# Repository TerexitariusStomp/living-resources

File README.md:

# living-resources

A living sensing commons: cheap, passive, **universal** field nodes relay
multimodal ecological detections over Reticulum to a Playnet edge, where
readings become witnessed receipts and receipts become credit for the
ecology that produced them.

License: AGPL-3.0-or-later.

## The node

One board, every lane's electronics populated (~$35–45 BOM):

camera (OV2640) · air mic (INMP441, 48 kHz/16-bit) · env
(BME280/BH1750/PIR) · hydrophone front-end · ultrasonic MEMS (20–100 kHz)
· C4D contactless front-end · 40 kHz emit transducer · microSD · Reticulum
(WiFi/LoRa/satellite)

A node's role is software + which head is in the environment — never a
different product. See `spec/living-resources.md`.

## The rules that make it a commons

- Every ecological subject is an agent with a human guardian and
  **voice 0** — it earns, it never speaks.
- `sense`/`fleet` lanes admit on **evidence** (a SAID on the lane's gate).
- `emit`/`cast`/`store` admit on **joint guardian+operator consent** —
  bio-write and cloud-write are decisions, not defaults.
- `hop`/`compute`/`engineered` refuse outright — consent is not evidence.
- Every refusal is a structured value; every emission is logged and
  receipted.

## Quickstart

```bash
make test                  # e2e under guile; static checks without it
make check-custom-budget   # the ≤5% first-party rule
```

E0 field validation (see `docs/EXPERIMENTS.md`): flash
`firmware/node/main.py` to a XIAO ESP32-S3 Sense, run the edge adapters
against the node's detection stream, score detections blinded.

## Layout

```
module/living/   specs · agents · sense-subject · attest · settlement · offers
adapters/        mic · camera · reticulum · weather   (thin seams; ML stays
                 Python-side)
firmware/node/   MicroPython universal node (incl. consent-gated EmitLane)
deploy/policies/ OPA: lane-gate.rego · consent.rego
spec/            the system spec
docs/            ARCHITECTURE (component map) · SCIENCE (claim table)
                 · EXPERIMENTS (E-gates) · ROADMAP · CONNECTOME
                 · EFFICIENCY · FUNDING (+ funding/ app drafts)
tests/e2e/       sensing-cell · refused-lanes · write-lanes
tools/edge/      classify.py (edge ML seam) · rns_edge.py (LXMF daemon)
tools/e0/        score.py (blinded field-validation scorer)
tools/e5/        relay_check.py (E5 hop-graduation harness)
```

## Non-interference

Passive by default: nothing attaches to an organism, nothing enters soil,
no anchor moorings, no flash or IR. Emission exists — it is a lane the
commons can ride — and it rides only on recorded joint consent, at
duty-cycled minimum power, with every burst on the ledger.

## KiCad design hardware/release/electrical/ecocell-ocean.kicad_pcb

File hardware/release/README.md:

# EcoCell Ocean — Engineering Release

This directory is the manufacturing package for the ocean-capable EcoCell
node: pressure-rated submerged electronics body plus a minimal-signature
tether float (GPS, antenna, solar). One serialized design covers both the
tether-float and fully submerged-pod forms — the same node electronics,
deployment role chosen by firmware flags.

## Release levels

- **R0 — prototype fab package.** A supplier-reviewable package a fab can
  quote and build from: native KiCad sources, netlist, DSN, Gerbers +
  drill, CPL, controlled BOM, assembly + harness drawings, stack-up/fab
  drawing, test plan, unit traveler, and this README with a checksummed
  manifest. R0 does **not** claim validated pressure rating, ecological
  benefit, or field performance — it claims the design files are
  consistent, DRC-clean, and buildable.
- **R1 — validated build.** R0 plus: assembled units pass TEST-PLAN,
  pressure/leak spec verified on the hull, Salton Sea serialized trial
  complete, DFM/DFT review closed with the supplier.

## Configuration identity

| Item | Value |
|---|---|
| Board | `ecocell-ocean` — 120 × 90 mm, 4-layer (F.Cu / In1 GND / In2 +3V3 / B.Cu) |
| Electrical rev | generated by `tools/pcb/gen_ocean_sch.py` + `gen_ocean_pcb.py` from the same netlist |
| Enclosure revision | `TBD` — pressure-hull + biota-disguised float CAD pending |
| Firmware revision | `firmware/node/main.py` as committed; image hash recorded per unit |
| Regional radio variant | `E22-400M22S` (433 MHz) or `E22-900M22S` (868/915) — one per build, declared |
| Approved suppliers | `TBD` — quote-backed, per-part, with lifecycle/stock check |

## Regenerating the electrical package

```
python3 tools/pcb/gen_ocean_sch.py          # writes electrical/ecocell-ocean.net
python3 tools/pcb/gen_ocean_pcb.py          # placement + DSN export
STITCH=1 python3 tools/pcb/gen_ocean_pcb.py # adds the stitch router (slow)
POST_ONLY=1 python3 tools/pcb/gen_ocean_pcb.py
    # resume: re-run only the post-attach island pass on the saved board
```

Fabrication rules baked into the generator: ≥0.2 mm clearance, ≥0.15 mm
track, 0.5/0.3 mm vias, ≥0.5 mm copper-to-edge, mounting-hole and
ESP32 antenna keepouts.

Known substitutions vs the ideal BOM:

| Ref | Part | Footprint used | Note |
|---|---|---|---|
| U_CHG | TP4056 | `SOIC-8-1EP_3.9x4.9mm_P1.27mm_EP2.41x3.81mm` | ESOP-8 footprint absent from stock KiCad libs; pin-compatible SOIC-8-EP used — verify land pattern against the chosen charger MPN before ordering |

## Release artifacts (required for R0)

| Artifact | Path / source | Status |
|---|---|---|
| Native KiCad schematic | `hardware/release/electrical/ecocell-ocean.kicad_sch` | **present** — `tools/pcb/net2sch.py` rebuilds it from `.net`; connectivity-exact (netlist round-trip: 79/79 nets, 0 diffs). Box symbols + net labels, not a redrawn sheet |
| Native KiCad PCB | `hardware/release/electrical/ecocell-ocean.kicad_pcb` | **verified** — DRC 0 unconnected / 0 errors / 0 warnings (`electrical/drc-report.txt`). **Canonical for fabrication** — `tools/pcb/gen_ocean_pcb.py` reproduces placement + route topology from the netlist, not the shipped copper; ECO fixes live only in this file |
| Gerbers + drill (or IPC-2581) | `hardware/release/electrical/fab/ecocell-ocean/` | **present** — 4-layer Gerbers + NPTH/PTH drills, sha256-manifested |
| Board stack-up / fab drawing | `hardware/release/FAB-NOTES.md` | **present** — stack-up + CAM notes; fiducials placed clear of the antenna keepout |
| Controlled BOM (MPN + alternates) | `hardware/release/electrical/ecocell-ocean-bom.csv` | **present** — generated from the netlist; MPNs/quoting unverified |
| CPL with verified origin/rotation | `hardware/release/electrical/fab/ecocell-ocean-cpl.csv` | **present** — exported from placed PCB; origin/rotation **unverified** against a supplier pick file |
| Assembly drawing | `hardware/release/assembly/` | **missing** |
| Fab quote bundle | `electrical/ecocell-ocean-fab.zip` | **present** — zipped Gerbers + drills + CPL + MANIFEST, Seeed-uploadable |
| Harness drawings | `hardware/release/HARNESS.md` | **present** — connector pinouts + tether spec from the netlist |
| Mechanical CAD + STEP + drawings | `hardware/release/mechanical/` | **present** — tube + end caps quote-ready STEP + scad source + dimensioned notes; float/dome/tether unmodeled |
| Pressure/leak spec | `hardware/release/PRESSURE-SPEC.md` | **present** — 0.4 MPa working / 0.6 MPa proof envelope; end-cap bending hand-calc closed, O-ring sizing per Parker done — FEA optional |
| Test fixture spec | `hardware/release/TEST-PLAN.md` | **present** |
| Unit traveler / calibration record | `hardware/release/UNIT-TRAVELER.md` | **present** |
| Firmware image + hash | `hardware/release/firmware-image.json` | **partial** — source-tree hash recorded; reproducible cross-build pending |
| Release manifest + checksums | `hardware/release/manifest.json` | **present** |
| DFM/DFT review record | `hardware/release/DFM-REVIEW.md` | **present** — self-review vs Seeed/JLCPCB published caps; supplier sign-off + DFT fixture still required |

No artifact may be silently replaced: any change goes through the ECO
procedure below and bumps the relevant revision.

## ECO procedure

1. Describe the change in `CHANGELOG.md` (rev, scope, reason, risk).
2. Regenerate affected artifacts from source — never hand-edit Gerbers,
   CPL, or the manifest.
3. Re-run DRC on the board and the repo checks (`make test`,
   `make check-custom-budget`); record results in the manifest.
4. Re-hash every shipped artifact into `manifest.json` and bump the
   package checksum.
5. A second reviewer signs off before the package is quoted to a fab.

## Honest-status notes

- The board validates as *fabrication-ready for a prototype lot*:
  DRC is clean (0 unconnected / 0 errors) and Gerbers + drills + CPL
  are exported and manifested. **Production** still gates on: supplier
  DFM/DFT review + quote-backed BOM, mechanical CAD (pressure hull +
  float), pressure/leak verification on the hull, a successful bring-up
  on the prototype lot, and second-reviewer sign-off per the ECO
  procedure. Never board-spun, never powered — treat the first lot as
  engineering prototypes, not saleable units.
- Acoustic playback hardware (emit lane) is consent-gated in firmware
  and policy; no ecological effect is claimed from this package.

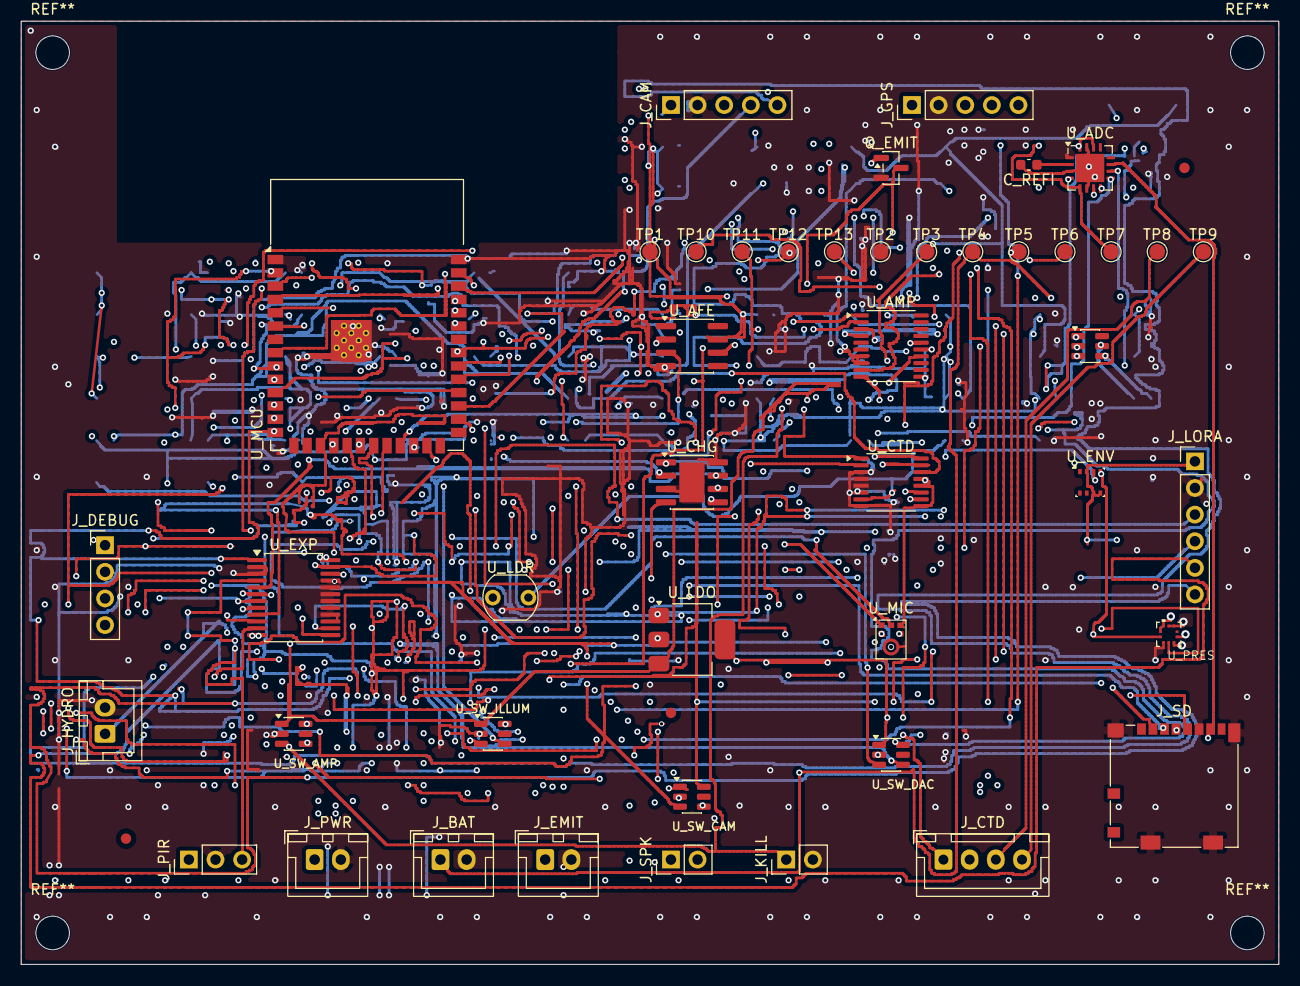
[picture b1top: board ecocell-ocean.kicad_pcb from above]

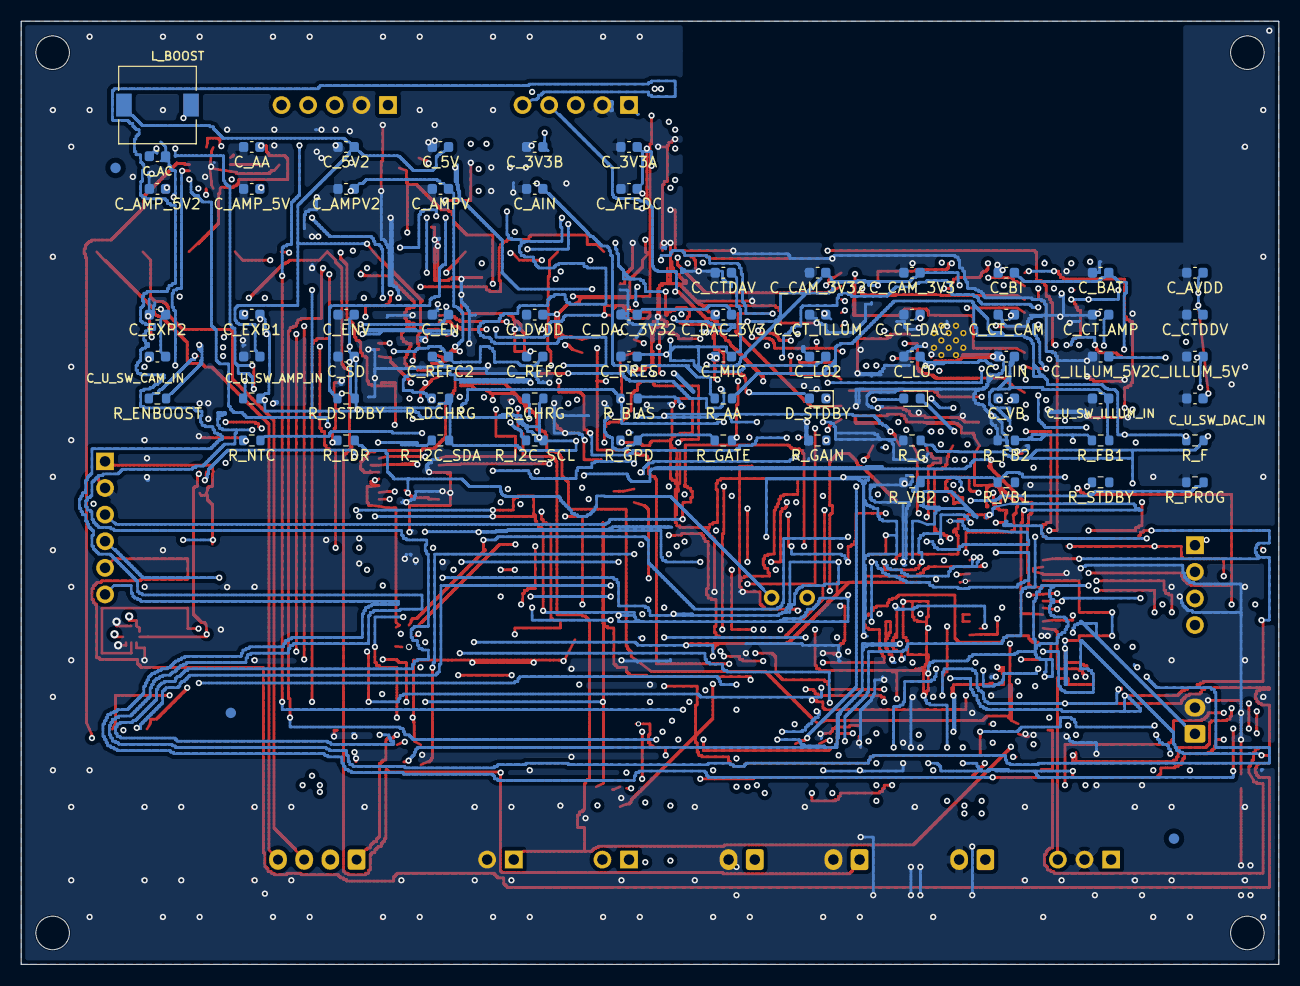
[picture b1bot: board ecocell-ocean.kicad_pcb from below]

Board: 4 copper layers, 120.0 x 90.0 mm, 121 parts (73 on the bottom side), 79 nets.

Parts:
C_3V3A, C_3V3B, C_5V, C_5V2: TPS27081A; C_0603_1608Metric
C_AA: TPS27081A; C_0603_1608Metric
C_AC: TPS27081A; C_0603_1608Metric
C_AFEDC: TPS27081A; C_0603_1608Metric
C_AIN: TPS27081A; C_0603_1608Metric
C_AMPV, C_AMPV2: TPS27081A; C_0603_1608Metric
C_AMP_5V, C_AMP_5V2: TPS27081A; C_0603_1608Metric
C_AVDD: TPS27081A; C_0603_1608Metric
C_BAT: TPS27081A; C_0603_1608Metric
C_BI: TPS27081A; C_0603_1608Metric
C_CAM_3V3, C_CAM_3V32: TPS27081A; C_0603_1608Metric
C_CTDAV: TPS27081A; C_0603_1608Metric
C_CTDDV: TPS27081A; C_0603_1608Metric
C_CT_AMP: TPS27081A; C_0603_1608Metric
C_CT_CAM: TPS27081A; C_0603_1608Metric
C_CT_DAC: TPS27081A; C_0603_1608Metric
C_CT_ILLUM: TPS27081A; C_0603_1608Metric
C_DAC_3V3, C_DAC_3V32: TPS27081A; C_0603_1608Metric
C_DVDD: TPS27081A; C_0603_1608Metric
C_EN: TPS27081A; C_0603_1608Metric
C_ENV: TPS27081A; C_0603_1608Metric
C_EXP1, C_EXP2: TPS27081A; C_0603_1608Metric
C_ILLUM_5V, C_ILLUM_5V2: TPS27081A; C_0603_1608Metric
C_LIN: TPS27081A; C_0603_1608Metric
C_LO, C_LO2: TPS27081A; C_0603_1608Metric
C_MIC: TPS27081A; C_0603_1608Metric
C_PRES: TPS27081A; C_0603_1608Metric
C_REFC, C_REFC2: TPS27081A; C_0603_1608Metric
C_REFI: 100nF; C_0603_1608Metric
C_SD: TPS27081A; C_0603_1608Metric
C_U_SW_AMP_IN: TPS27081A; C_0603_1608Metric
C_U_SW_CAM_IN: TPS27081A; C_0603_1608Metric
C_U_SW_DAC_IN: TPS27081A; C_0603_1608Metric
C_U_SW_ILLUM_IN: TPS27081A; C_0603_1608Metric
C_VB: TPS27081A; C_0603_1608Metric
D_CHRG: TPS27081A; LED_0603_1608Metric
D_STDBY: TPS27081A; LED_0603_1608Metric
FID1, FID2, FID3, FID4, FID5, FID6: Fiducial_1mm_Mask2mm
J_BAT: BAT; JST_XH_B2B-XH-A_1x02_P2.50mm_Vertical
J_CAM: CAM; PinHeader_1x05_P2.54mm_Vertical
J_CTD: CTD; JST_XH_B4B-XH-A_1x04_P2.50mm_Vertical
J_DEBUG: DEBUG; PinHeader_1x04_P2.54mm_Vertical
J_EMIT: EMIT; JST_XH_B2B-XH-A_1x02_P2.50mm_Vertical
J_GPS: GPS; PinHeader_1x05_P2.54mm_Vertical
J_HYDRO: HYDRO; JST_XH_B2B-XH-A_1x02_P2.50mm_Vertical
J_KILL: KILL; PinHeader_1x02_P2.54mm_Vertical
J_LORA: LORA; PinHeader_1x06_P2.54mm_Vertical
J_PIR: PIR; PinHeader_1x03_P2.54mm_Vertical
J_PWR: PWR; JST_XH_B2B-XH-A_1x02_P2.50mm_Vertical
J_SD: microSD; microSD_HC_Molex_104031-0811
J_SPK: SPK; PinHeader_1x02_P2.54mm_Vertical
L_BOOST: TPS27081A; L_7.3x7.3_H4.5
Q_EMIT: 2N7002; SOT-23
R_AA: TPS27081A; R_0603_1608Metric
R_BIAS: TPS27081A; R_0603_1608Metric
R_CHRG: TPS27081A; R_0603_1608Metric
R_DCHRG: TPS27081A; R_0603_1608Metric
R_DSTDBY: TPS27081A; R_0603_1608Metric
R_EN: TPS27081A; R_0603_1608Metric
R_ENBOOST: TPS27081A; R_0603_1608Metric
R_F: TPS27081A; R_0603_1608Metric
R_FB1, R_FB2: TPS27081A; R_0603_1608Metric
R_G: TPS27081A; R_0603_1608Metric
R_GAIN: TPS27081A; R_0603_1608Metric
R_GATE: TPS27081A; R_0603_1608Metric
R_GPD: TPS27081A; R_0603_1608Metric
R_I2C_SCL, R_I2C_SDA: TPS27081A; R_0603_1608Metric
R_LDR: TPS27081A; R_0603_1608Metric
R_NTC: TPS27081A; R_0603_1608Metric
R_PROG: TPS27081A; R_0603_1608Metric
R_STDBY: TPS27081A; R_0603_1608Metric
R_VB1, R_VB2: TPS27081A; R_0603_1608Metric
TP1, TP2, TP3, TP4, TP5, TP6, TP7, TP8, TP9, TP10, TP11, TP12, TP13: TP; TestPoint_Pad_D1.5mm
U_ADC: ADS8681; QFN-16-1EP_4x4mm_P0.65mm_EP2.7x2.7mm
U_AFE: OPA333; SOIC-8_3.9x4.9mm_P1.27mm
U_AMP: PCM5102A; TSSOP-20_4.4x6.5mm_P0.65mm
U_BOOST: MT3608; SOT-23-6
U_CHG: TP4056; SOIC-8-1EP_3.9x4.9mm_P1.27mm_EP2.41x3.81mm
U_CTD: ADS1220; TSSOP-16_4.4x5mm_P0.65mm
U_ENV: BME280; Bosch_LGA-8_2.5x2.5mm_P0.65mm_ClockwisePinNumbering
U_EXP: TCA9535DBT; SSOP-24_5.3x8.2mm_P0.65mm
U_LDO: AMS1117-3.3; SOT-223-3_TabPin2
U_LDR: GL5528; R_LDR_5.1x4.3mm_P3.4mm_Vertical
U_MCU: ESP32-S3-WROOM-1
U_MIC: ICS-43434; InvenSense_ICS-43434-6_3.5x2.65mm
U_PRES: BMP390; BMP390_LGA-10_2x2mm
U_SW_AMP: TPS27081A; SOT-23-6
U_SW_CAM: TPS27081A; SOT-23-6
U_SW_DAC: TPS27081A; SOT-23-6
U_SW_ILLUM: TPS27081A; SOT-23-6

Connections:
+3V3: C_3V3A.1, C_3V3B.1, C_AFEDC.1, C_AVDD.1, C_CTDAV.1, C_CTDDV.1, C_DVDD.1, C_ENV.1, C_EXP1.1, C_EXP2.1, C_LO.1, C_LO2.1, C_MIC.1, C_PRES.1, C_SD.1, C_U_SW_CAM_IN.1, C_U_SW_DAC_IN.1, J_DEBUG.1, J_GPS.1, J_LORA.1, J_PIR.1, J_SD.4, R_CHRG.1, R_DCHRG.1, R_DSTDBY.1, R_EN.1, R_I2C_SCL.1, R_I2C_SDA.1, TP1.1, U_ADC.14, U_ADC.16, U_AFE.7, U_AMP.4, U_CTD.9, U_CTD.12, U_CTD.13, U_ENV.2, U_ENV.5, U_ENV.6, U_EXP.24, U_LDO.2, U_LDR.1, U_MCU.2, U_MIC.5, U_PRES.1, U_PRES.6, U_PRES.10, U_SW_CAM.1, U_SW_DAC.1
+5V: C_5V.1, C_5V2.1, C_LIN.1, C_U_SW_AMP_IN.1, C_U_SW_ILLUM_IN.1, L_BOOST.2, R_FB1.1, TP3.1, U_LDO.3, U_SW_AMP.1, U_SW_ILLUM.1
ADC_AIN: C_AA.1, C_AIN.1, R_AA.2, TP7.1, U_ADC.5
ADC_RST: U_ADC.7, U_MCU.8
ADS_CS: U_CTD.2, U_MCU.25
ADS_DIN: U_CTD.16, U_MCU.23
ADS_DOUT: U_CTD.15, U_MCU.24
ADS_DRDY: U_CTD.14, U_MCU.28
ADS_SCK: U_CTD.1, U_MCU.11
AFE_INP: C_AC.2, R_BIAS.2, U_AFE.3
AFE_N: R_F.1, R_G.1, U_AFE.2
AFE_OUT: R_AA.1, R_F.2, TP6.1, U_AFE.6
AMP_5V: C_AMPV.1, C_AMPV2.1, C_AMP_5V.1, C_AMP_5V2.1, U_AMP.7, U_AMP.8, U_SW_AMP.6
CAM_3V3: C_CAM_3V3.1, C_CAM_3V32.1, J_CAM.1, U_SW_CAM.6
CAM_RST: J_CAM.5, U_EXP.11
CHRG_ST: D_CHRG.1, R_CHRG.2, U_CHG.7, U_EXP.5
CTD_EXC_N: J_CTD.4, TP9.1
CTD_EXC_P: J_CTD.3, TP8.1
CTD_S_N: J_CTD.2, U_CTD.10
CTD_S_P: J_CTD.1, U_CTD.11
CT_AMP: C_CT_AMP.1, U_SW_AMP.4
CT_CAM: C_CT_CAM.1, U_SW_CAM.4
CT_DAC: C_CT_DAC.1, U_SW_DAC.4
CT_ILLUM: C_CT_ILLUM.1, U_SW_ILLUM.4
DAC_3V3: C_DAC_3V3.1, C_DAC_3V32.1, U_SW_DAC.6
DEBUG_RX: J_DEBUG.4, U_MCU.36
DEBUG_TX: J_DEBUG.3, U_MCU.37
EMIT_GATE: Q_EMIT.1, R_GATE.2, R_GPD.1
EMIT_PWM: R_GATE.1, U_MCU.39
EMIT_SIG: J_EMIT.1, Q_EMIT.3
EN: C_EN.1, R_EN.2, U_MCU.3
EN_AMP: J_KILL.1, TP11.1, U_EXP.8, U_SW_AMP.3
EN_BOOST: R_ENBOOST.2, U_BOOST.4
EN_CAM: TP10.1, U_EXP.7, U_SW_CAM.3
EN_ILLUM: TP12.1, U_EXP.9, U_SW_ILLUM.3
EN_PLAY: TP13.1, U_EXP.10, U_SW_DAC.3
EXP_INT: U_EXP.1, U_MCU.14
FB: R_FB1.2, R_FB2.1, U_BOOST.3
GAIN_SLOT: R_GAIN.1, U_AMP.2
GND: C_3V3A.2, C_3V3B.2, C_5V.2, C_5V2.2, C_AA.2, C_AFEDC.2, C_AIN.2, C_AMPV.2, C_AMPV2.2, C_AMP_5V.2, C_AMP_5V2.2, C_AVDD.2, C_BAT.2, C_BI.2, C_CAM_3V3.2, C_CAM_3V32.2, C_CTDAV.2, C_CTDDV.2, C_CT_AMP.2, C_CT_CAM.2, C_CT_DAC.2, C_CT_ILLUM.2, C_DAC_3V3.2, C_DAC_3V32.2, C_DVDD.2, C_EN.2, C_ENV.2, C_EXP1.2, C_EXP2.2, C_ILLUM_5V.2, C_ILLUM_5V2.2, C_LIN.2, C_LO.2, C_LO2.2, C_MIC.2, C_PRES.2, C_REFC.2, C_REFC2.2, C_REFI.2, C_SD.2, C_U_SW_AMP_IN.2, C_U_SW_CAM_IN.2, C_U_SW_DAC_IN.2, C_U_SW_ILLUM_IN.2, C_VB.2, J_BAT.2, J_CAM.2, J_DEBUG.2, J_EMIT.2, J_GPS.2, J_HYDRO.2, J_KILL.2, J_LORA.2, J_PIR.2, J_PWR.2, J_SD.6, J_SD.SH, Q_EMIT.2, R_FB2.2, R_G.2, R_GAIN.2, R_GPD.2, R_LDR.2, R_NTC.2, R_PROG.2, R_VB2.2, TP2.1, U_ADC.1, U_ADC.3, U_ADC.6, U_ADC.15, U_ADC.17, U_AFE.4, U_AMP.3, U_AMP.11, U_AMP.15, U_BOOST.2, U_CHG.3, U_CHG.8, U_CHG.9, U_CTD.3, U_CTD.4, U_CTD.5, U_CTD.6, U_CTD.8, U_EXP.2, U_EXP.3, U_EXP.12, U_EXP.15, U_EXP.16, U_EXP.17, U_EXP.18, U_EXP.19, U_EXP.20, U_EXP.21, U_LDO.1, U_MCU.1, U_MCU.40, U_MCU.41, U_MIC.2, U_MIC.3, U_PRES.3, U_PRES.5, U_PRES.8, U_PRES.9, U_SW_AMP.2, U_SW_CAM.2, U_SW_DAC.2, U_SW_ILLUM.2
HYDRO_SIG: C_AC.1, J_HYDRO.1
I2C_SCL: R_I2C_SCL.2, U_ENV.4, U_EXP.22, U_MCU.17, U_PRES.2
I2C_SDA: R_I2C_SDA.2, U_ENV.3, U_EXP.23, U_MCU.12, U_PRES.4
I2S0_BCLK: U_MCU.18, U_MIC.4
I2S0_SD: U_MCU.13, U_MIC.6
I2S0_WS: U_MCU.10, U_MIC.1
I2S1_BCLK: U_AMP.16, U_MCU.4
I2S1_DIN: U_AMP.1, U_MCU.6
I2S1_LRCK: U_AMP.14, U_MCU.5
ILLUM_5V: C_ILLUM_5V.1, C_ILLUM_5V2.1, U_SW_ILLUM.6
LDR_OUT: R_LDR.1, U_CTD.7, U_LDR.2
LED_CHRG_A: D_CHRG.2, R_DCHRG.2
LED_STDBY_A: D_STDBY.2, R_DSTDBY.2
LORA_M0: J_LORA.5, U_EXP.13
LORA_M1: J_LORA.6, U_EXP.14
NTC: R_NTC.1, U_CHG.1
PIR_OUT: J_PIR.3, U_EXP.4
PPS: J_GPS.5, U_MCU.29
PROG: R_PROG.1, U_CHG.2
REFCAP: C_REFC.1, C_REFC2.1, U_ADC.4
REFIO: C_REFI.1, U_ADC.2
SD_CS: J_SD.2, U_MCU.38
SPI2_CS: U_ADC.9, U_MCU.22
SPI2_MISO: J_SD.7, U_ADC.11, U_MCU.21
SPI2_MOSI: J_SD.3, U_ADC.8, U_MCU.19
SPI2_SCK: J_SD.5, U_ADC.10, U_MCU.20
SPK_N: J_SPK.2, U_AMP.10
SPK_P: J_SPK.1, U_AMP.9
STDBY_ST: D_STDBY.1, R_STDBY.2, U_CHG.6, U_EXP.6
SW: L_BOOST.1, U_BOOST.1
UART1_RX: J_LORA.3, U_MCU.30
UART1_TX: J_LORA.4, U_MCU.33
UART2_RX: J_GPS.3, U_MCU.31
UART2_TX: J_GPS.4, U_MCU.35
UART3_RX: J_CAM.3, U_MCU.32
UART3_TX: J_CAM.4, U_MCU.9
VBAT: C_BAT.1, C_BI.1, J_BAT.1, R_ENBOOST.1, TP4.1, U_BOOST.5, U_CHG.5
VBIAS: C_VB.1, R_BIAS.1, R_VB1.2, R_VB2.1, TP5.1
VIN: J_PWR.1, U_CHG.4

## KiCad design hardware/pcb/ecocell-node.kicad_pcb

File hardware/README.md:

# hardware/ — EcoCell universal node

One board design. Every lane's electronics on every unit. Role =
firmware config + which head sits in the environment — never a variant,
never an upgrade purchase.

## What to read in what order

| File | For |
|---|---|
| `BOM.md` | What to buy — core board + every head + per-deployment kits |
| `FIELD-KIT.md` | **Complete sourcing matrix** — Seeed-assembled vs plug-in vs field kit, first-article test plan |
| `PROVISIONING.md` | **Parcel→live node** — flash, identity, consent defaults, edge pairing, commissioning |
| `PINOUT.md` | How it wires — the pin map the firmware and heads share |
| `ASSEMBLY.md` | How to build — solder points, flash steps, bench test |
| `ENCLOSURE.md` | How to deploy — garden / shore-dock / reef-float / submerged forms |
| `DATASHEET.md` | The tender-attachable product sheet (prospective — v1 target) |
| `PCB.md` | **Manufacturable carrier** — KiCad source, DRC-clean Gerbers, Seeed ordering |
| `diagrams/wiring.svg` | **Visual: full wiring diagram** — every pin→head wire, net colors |
| `diagrams/layout.svg` | **Visual: carrier top-view** — component placement on perfboard |
| `diagrams/enclosure-forms.svg` | **Visual: 4 cross-sections** — garden/shore/float/pod |

## The build in one picture

```
        ┌──────────────────── XIAO ESP32-S3 Sense ───────────────────┐
        │  onboard: OV2640 camera · PDM mic · microSD · ESP32-S3     │
        │                                                           │
  D0 PIR wake ──┐            ┌── D4/D5  I2C bus ──────────────────┐  │
  D1 hydro ADC  │            │  BME280 · BH1750 · AD7746 (C4D)    │  │
  D2 ultra ADC  │            └────────────────────────────────────┘  │
  D3 emit PWM ──┼──▶ 40 kHz transducer driver (consent-gated)        │
  D6/D7 UART ───┼──▶ LoRa RNode / satellite modem / serial gateway   │
  D8–D10 SPI ───┴──▶ spare (expansion: second SD, display, GPS)      │
        └───────────────────────────────────────────────────────────┘
```

## Two build paths

1. **Hand build (v1, now):** XIAO ESP32-S3 Sense + breakout modules on
   headers — no PCB fab needed, ~1–2 h per unit, ~$35–45.
2. **Carrier board (v2, tender path):** `pcb/` holds a **DRC-clean,
   fab-ready KiCad design** — upload `gerbers/ecocell-carrier-gerbers.zip`
   to Seeed Fusion (2-layer, 100×80, standard spec). v2 adds the field
   layer: screw-terminal 5V input, fuse, reverse-polarity Schottky, rail
   TVS, ESD clamps on the head inputs, power LED, fiducials. See `PCB.md`
   for the package and `FIELD-KIT.md` for everything else a deployable
   node still needs (XIAO, heads, radio, power, enclosure).

## Honest flags

- Pin assignments in `PINOUT.md` are the recommended map — **verify the
  free-GPIO set against your board revision's schematic** (XIAO Sense
  expansion board occupies internal pins for camera/mic/SD).
- The ultrasonic lane's 20–100 kHz band exceeds what the ESP32 ADC path
  samples comfortably — the head and wiring are ready; firmware capture
  may need decimation tricks or the C++ firmware variant. Noted in
  `PINOUT.md`, not hidden.
- Emit lane: hardware is live on every board; activation is purely a
  consent flag — see `deploy/policies/living/` and `firmware/node/main.py`.

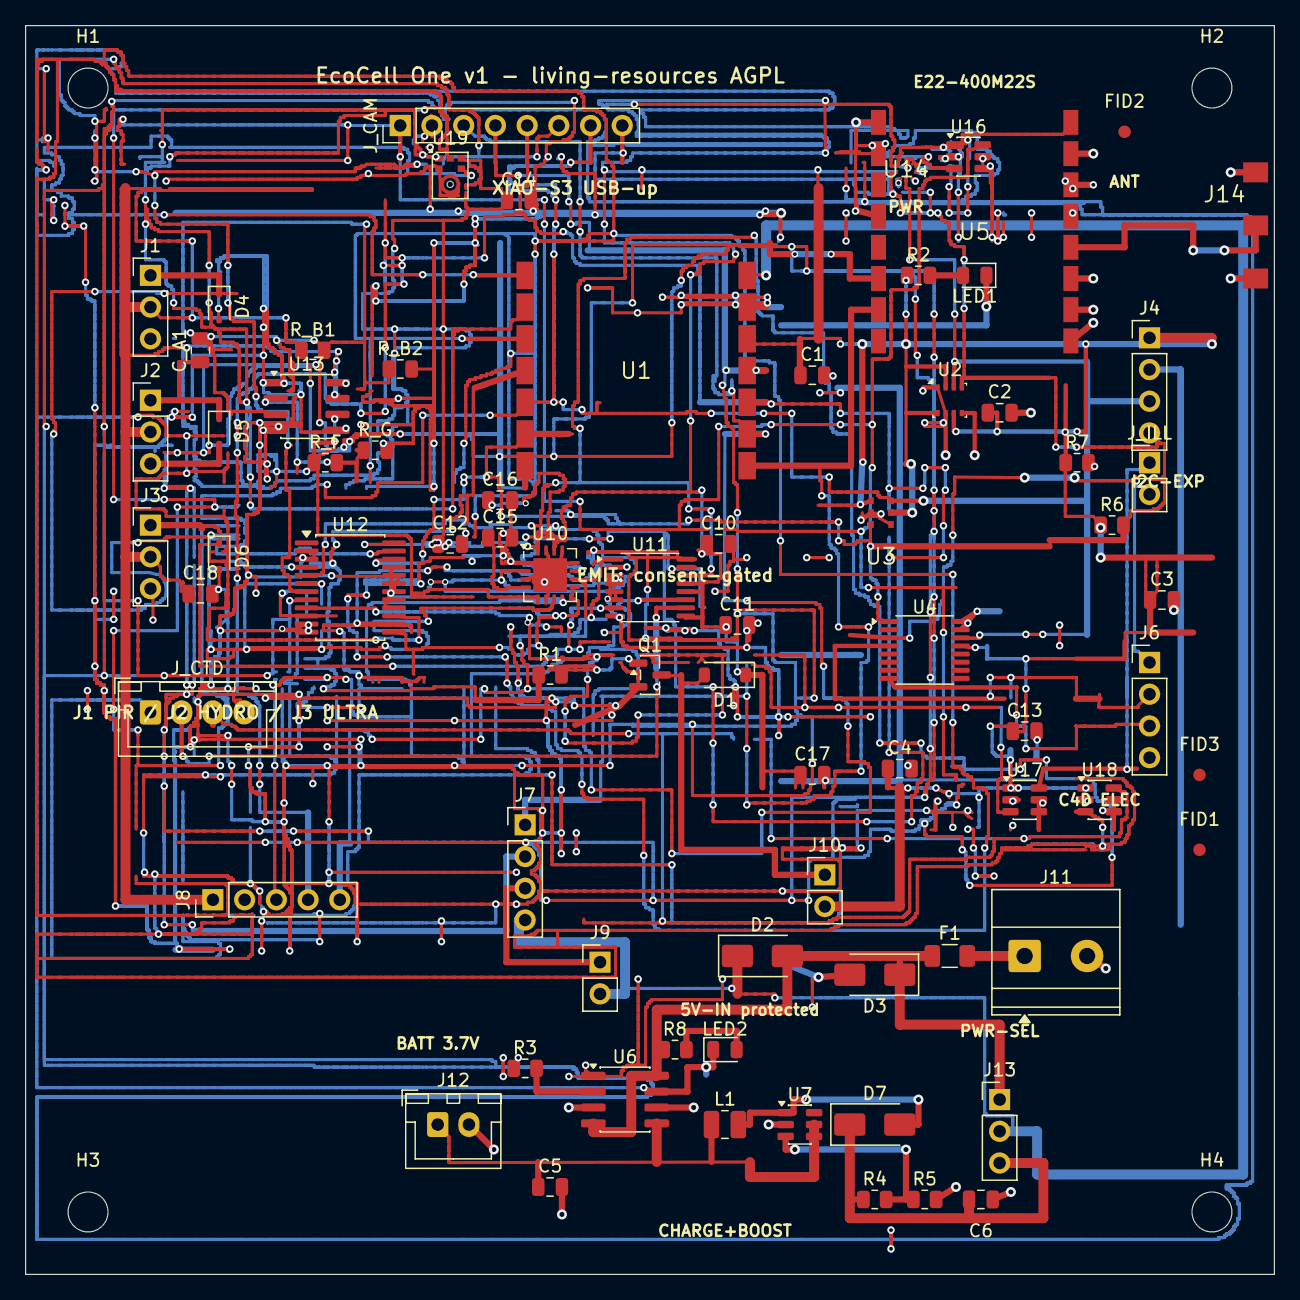
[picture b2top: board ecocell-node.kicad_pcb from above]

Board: 2 copper layers, 100.0 x 100.0 mm, 79 parts (0 on the bottom side), 51 nets.

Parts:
C1, C2, C3, C4, C10, C11, C12, C13, C14, C17, C18: 100nF; C_0805_2012Metric
C5, C6: 22uF; C_0805_2012Metric
C15, C16: 10uF; C_0805_2012Metric
C_A1: 1uF; C_0805_2012Metric
D1: 1N4148W; D_SOD-123
D2, D7: SS14; D_SMA
D3: SMAJ5.0A; D_SMA
D4, D5, D6: PESD5V0; D_SOD-323
F1: 0.75A; Fuse_1206_3216Metric
FID1, FID2, FID3: FID; Fiducial_1mm_Mask3mm
H1, H2, H3, H4: M3; MountingHole_3.2mm_M3
J1: PIR; PinHeader_1x03_P2.54mm_Vertical
J2: HYDRO; PinHeader_1x03_P2.54mm_Vertical
J3: ULTRA; PinHeader_1x03_P2.54mm_Vertical
J4: I2C-EXP; PinHeader_1x04_P2.54mm_Vertical
J6: C4D-ELEC; PinHeader_1x04_P2.54mm_Vertical
J7: UART; PinHeader_1x04_P2.54mm_Vertical
J8: SPI; PinHeader_1x05_P2.54mm_Vertical
J9: 5V-IN; PinHeader_1x02_P2.54mm_Vertical
J10: EMIT-40k; PinHeader_1x02_P2.54mm_Vertical
J11: 5V-SCREW; TerminalBlock_Phoenix_MKDS-1,5-2_1x02_P5.00mm_Horizontal
J12: BATT-3.7V; JST_XH_B2B-XH-A_1x02_P2.50mm_Vertical
J13: PWR-SEL; PinHeader_1x03_P2.54mm_Vertical
J14: SMA-EDGE
J_CAM: CAM-SPI; PinHeader_1x08_P2.54mm_Vertical
J_CTD: CTD; JST_XH_B4B-XH-A_1x04_P2.50mm_Vertical
J_ILL: ILLUM; PinHeader_1x02_P2.54mm_Vertical
L1: 22uH; L_1008_2520Metric
LED1: PWR-GRN; LED_0805_2012Metric
LED2: CHRG-RED; LED_0805_2012Metric
Q1: 2N7002; SOT-23
R1: 100R; R_0805_2012Metric
R2, R8: 1k; R_0805_2012Metric
R3: 1.2k; R_0805_2012Metric
R4: 75k; R_0805_2012Metric
R5: 10k; R_0805_2012Metric
R6, R7: 4.7k; R_0805_2012Metric
R_B1, R_B2: 100k; R_0805_2012Metric
R_F: 49.9k; R_0805_2012Metric
R_G: 1k; R_0805_2012Metric
U1: XIAO-ESP32S3
U2: BME280; Bosch_LGA-8_2.5x2.5mm_P0.65mm_ClockwisePinNumbering
U3: BH1750
U4: AD7746; TSSOP-16_4.4x5mm_P0.65mm
U5: E22-400M22S
U6: TP4056; SOP-8_3.76x4.96mm_P1.27mm
U7: MT3608; SOT-23-6
U10: ADS8681; QFN-16-1EP_4x4mm_P0.65mm_EP2.7x2.7mm
U11: ADS1220; TSSOP-16_4.4x5mm_P0.65mm
U12: TCA9535; SSOP-24_5.3x8.2mm_P0.65mm
U13: OPA333; SOIC-8_3.9x4.9mm_P1.27mm
U14: BMP390; BMP390_LGA-10_2x2mm
U16, U17, U18: TPS27081A; SOT-23-6
U19: ICS-43434; InvenSense_ICS-43434-6_3.5x2.65mm

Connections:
+3V3: C1.1, C2.1, C3.1, C4.1, C10.1, C11.1, C12.1, C13.1, C14.1, C17.1, C18.1, D1.1, J1.2, J2.2, J3.2, J4.1, J8.1, J10.2, R2.1, R6.1, R7.1, R_B1.1, U1.10, U2.2, U2.6, U2.8, U3.1, U3.5, U4.13, U5.9, U10.14, U10.16, U11.9, U11.12, U11.13, U12.24, U13.7, U14.1, U14.6, U14.10, U16.1, U17.1, U18.1, U19.5
+5V: D2.1, J7.4, J9.2, J13.2, U1.8
ADC_CS: U10.9, U12.13
ADC_RST: U10.7, U12.6
AFE_INP: C_A1.2, R_B1.2, R_B2.1, U13.3
AFE_N: R_F.2, R_G.1, U13.2
AFE_SRC: C_A1.1, D5.1, J2.1
AIN: R_F.1, U10.5, U13.6
ANT: J14.1, U5.13
CAM_3V3: J_CAM.1, U16.6
CAM_CS: J_CAM.6, U12.7
CHRG_LED: LED2.2, R8.2
CHRG_N: LED2.1, U6.7, U12.15
CIN_P: J6.3, U4.8
CTDEXC: J_CTD.3, U18.6
CTD_CS: U11.2, U12.14
CTD_DRDY: U11.14, U12.5
CTD_N: J_CTD.2, U11.10
CTD_P: J_CTD.1, U11.11
D3_EMIT: R1.1, U1.4
EMIT_GATE: Q1.1, R1.2
EMIT_SW: D1.2, J10.1, Q1.3
EN_CAM: U12.8, U16.3
EN_CTD: U12.10, U18.3
EN_ILLUM: U12.9, U17.3
EXC_A: J6.1, U4.3
EXC_B: J6.2, U4.4
FB_NODE: R4.2, R5.1, U7.3
GND: C1.2, C2.2, C3.2, C4.2, C5.2, C6.2, C10.2, C11.2, C12.2, C13.2, C14.2, C15.2, C16.2, C17.2, C18.2, D3.2, D4.2, D5.2, D6.2, J1.3, J2.3, J3.3, J4.2, J6.4, J7.3, J8.2, J9.1, J11.2, J12.2, J14.2, J_CAM.2, J_CTD.4, J_ILL.2, LED1.1, Q1.2, R3.1, R5.2, R_B2.2, R_G.2, U1.9, U2.1, U2.5, U2.7, U3.2, U3.4, U4.15, U4.16, U5.1, U5.2, U5.4, U5.10, U5.11, U5.12, U5.14, U5.15, U5.16, U6.1, U6.3, U6.6, U7.2, U10.1, U10.3, U10.6, U10.12, U10.13, U10.15, U10.17, U11.3, U11.4, U11.5, U11.6, U11.8, U12.2, U12.3, U12.11, U12.12, U12.16, U12.17, U12.18, U12.19, U12.20, U12.21, U13.1, U13.4, U13.5, U13.8, U14.3, U14.5, U14.7, U14.8, U14.9, U16.2, U16.4, U16.5, U17.2, U17.4, U17.5, U18.2, U18.4, U18.5, U19.2, U19.3
I2S_BCK: U1.1, U19.4
I2S_SD: U1.3, U19.6
I2S_WS: U1.2, U19.1
ILLUM_3V3: J_ILL.1, U17.6
LEDPWR: LED1.2, R2.2
MISO_D9: J8.4, J_CAM.5, U1.12, U10.11, U11.15
MOSI_D10: J8.3, J_CAM.4, U1.11, U10.8, U11.16
PIR_IN: D4.1, J1.1, U12.4
PROG_N: R3.2, U6.2
REFCAP: C15.1, U10.4
REFIO: C16.1, U10.2
RX_D7: J7.1, U1.14, U5.7
SCK_D8: J8.5, J_CAM.3, U1.13, U10.10, U11.1
SCL: J4.4, J_CAM.8, R6.2, U1.6, U2.4, U3.3, U4.1, U12.22, U14.2
SDA: J4.3, J_CAM.7, R7.2, U1.5, U2.3, U3.6, U4.14, U12.23, U14.4
SW_NODE: D7.2, L1.2, U7.1
TX_D6: J7.2, U1.7, U5.6
ULT_AIN: D6.1, J3.1, U11.7
VBATT: C5.1, J12.1, L1.1, U6.5, U7.4, U7.5
VBOOST: C6.1, D7.1, J13.3, R4.1
VIN: F1.2, J11.1
VPROT: D2.2, D3.1, F1.1, J13.1, R8.1, U6.4, U6.8

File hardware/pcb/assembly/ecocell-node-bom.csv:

Reference,Value,Footprint
C1,100nF,C_0805_2012Metric
C10,100nF,C_0805_2012Metric
C11,100nF,C_0805_2012Metric
C12,100nF,C_0805_2012Metric
C13,100nF,C_0805_2012Metric
C14,100nF,C_0805_2012Metric
C15,10uF,C_0805_2012Metric
C16,10uF,C_0805_2012Metric
C17,100nF,C_0805_2012Metric
C18,100nF,C_0805_2012Metric
C2,100nF,C_0805_2012Metric
C3,100nF,C_0805_2012Metric
C4,100nF,C_0805_2012Metric
C5,22uF,C_0805_2012Metric
C6,22uF,C_0805_2012Metric
C_A1,1uF,C_0805_2012Metric
D1,1N4148W,D_SOD-123
D2,SS14,D_SMA
D3,SMAJ5.0A,D_SMA
D4,PESD5V0,D_SOD-323
D5,PESD5V0,D_SOD-323
D6,PESD5V0,D_SOD-323
D7,SS14,D_SMA
F1,0.75A,Fuse_1206_3216Metric
J1,PIR,PinHeader_1x03_P2.54mm_Vertical
J10,EMIT-40k,PinHeader_1x02_P2.54mm_Vertical
J11,5V-SCREW,"TerminalBlock_Phoenix_MKDS-1,5-2_1x02_P5.00mm_Horizontal"
J12,BATT-3.7V,JST_XH_B2B-XH-A_1x02_P2.50mm_Vertical
J13,PWR-SEL,PinHeader_1x03_P2.54mm_Vertical
J14,SMA-EDGE,
J2,HYDRO,PinHeader_1x03_P2.54mm_Vertical
J3,ULTRA,PinHeader_1x03_P2.54mm_Vertical
J4,I2C-EXP,PinHeader_1x04_P2.54mm_Vertical
J6,C4D-ELEC,PinHeader_1x04_P2.54mm_Vertical
J7,UART,PinHeader_1x04_P2.54mm_Vertical
J8,SPI,PinHeader_1x05_P2.54mm_Vertical
J9,5V-IN,PinHeader_1x02_P2.54mm_Vertical
J_CAM,CAM-SPI,PinHeader_1x08_P2.54mm_Vertical
J_CTD,CTD,JST_XH_B4B-XH-A_1x04_P2.50mm_Vertical
J_ILL,ILLUM,PinHeader_1x02_P2.54mm_Vertical
L1,22uH,L_1008_2520Metric
LED1,PWR-GRN,LED_0805_2012Metric
LED2,CHRG-RED,LED_0805_2012Metric
Q1,2N7002,SOT-23
R1,100R,R_0805_2012Metric
R2,1k,R_0805_2012Metric
R3,1.2k,R_0805_2012Metric
R4,75k,R_0805_2012Metric
R5,10k,R_0805_2012Metric
R6,4.7k,R_0805_2012Metric
R7,4.7k,R_0805_2012Metric
R8,1k,R_0805_2012Metric
R_B1,100k,R_0805_2012Metric
R_B2,100k,R_0805_2012Metric
R_F,49.9k,R_0805_2012Metric
R_G,1k,R_0805_2012Metric
U1,XIAO-ESP32S3,
U10,ADS8681,QFN-16-1EP_4x4mm_P0.65mm_EP2.7x2.7mm
U11,ADS1220,TSSOP-16_4.4x5mm_P0.65mm
U12,TCA9535,SSOP-24_5.3x8.2mm_P0.65mm
U13,OPA333,SOIC-8_3.9x4.9mm_P1.27mm
U14,BMP390,BMP390_LGA-10_2x2mm
U16,TPS27081A,SOT-23-6
U17,TPS27081A,SOT-23-6
U18,TPS27081A,SOT-23-6
U19,ICS-43434,InvenSense_ICS-43434-6_3.5x2.65mm
U2,BME280,Bosch_LGA-8_2.5x2.5mm_P0.65mm_ClockwisePinNumbering
U3,BH1750,
U4,AD7746,TSSOP-16_4.4x5mm_P0.65mm
U5,E22-400M22S,
U6,TP4056,SOP-8_3.76x4.96mm_P1.27mm
U7,MT3608,SOT-23-6

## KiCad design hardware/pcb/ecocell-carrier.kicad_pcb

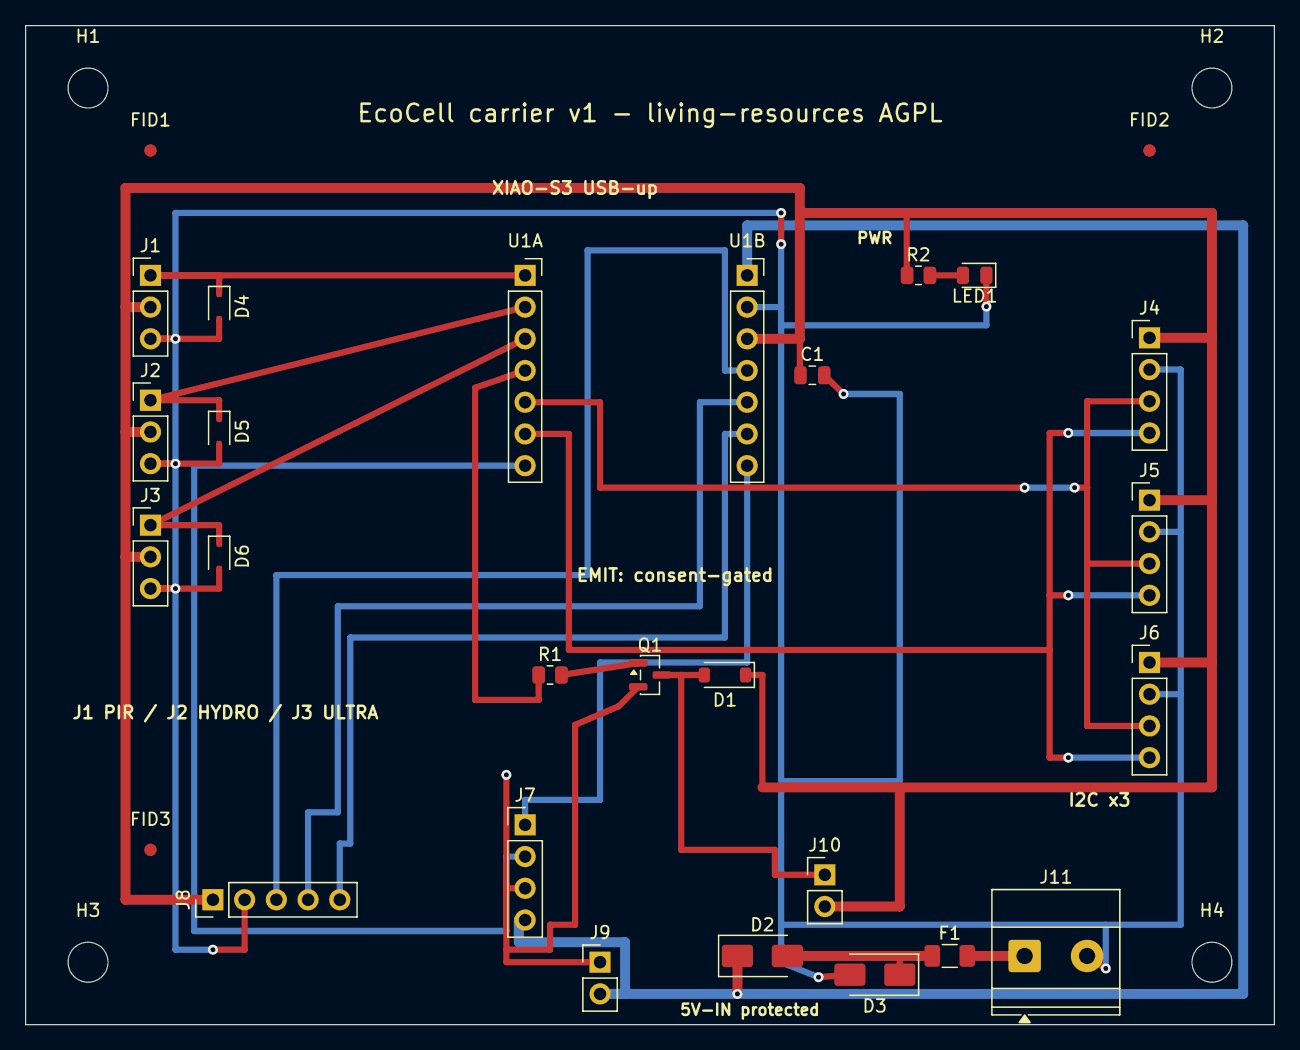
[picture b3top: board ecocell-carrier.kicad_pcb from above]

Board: 2 copper layers, 100.0 x 80.0 mm, 32 parts (0 on the bottom side), 19 nets.

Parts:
C1: 100nF; C_0805_2012Metric
D1: 1N4148W; D_SOD-123
D2: SS14; D_SMA
D3: SMAJ5.0A; D_SMA
D4, D5, D6: PESD5V0; D_SOD-323
F1: 0.75A; Fuse_1206_3216Metric
FID1, FID2, FID3: FID; Fiducial_1mm_Mask3mm
H1, H2, H3, H4: M3; MountingHole_3.2mm_M3
J1: PIR; PinHeader_1x03_P2.54mm_Vertical
J2: HYDRO; PinHeader_1x03_P2.54mm_Vertical
J3: ULTRA; PinHeader_1x03_P2.54mm_Vertical
J4: I2C-BME280; PinHeader_1x04_P2.54mm_Vertical
J5: I2C-BH1750; PinHeader_1x04_P2.54mm_Vertical
J6: I2C-AD7746; PinHeader_1x04_P2.54mm_Vertical
J7: UART; PinHeader_1x04_P2.54mm_Vertical
J8: SPI; PinHeader_1x05_P2.54mm_Vertical
J9: 5V-IN; PinHeader_1x02_P2.54mm_Vertical
J10: EMIT-40k; PinHeader_1x02_P2.54mm_Vertical
J11: 5V-SCREW; TerminalBlock_Phoenix_MKDS-1,5-2_1x02_P5.00mm_Horizontal
LED1: PWR-GRN; LED_0805_2012Metric
Q1: 2N7002; SOT-23
R1: 100R; R_0805_2012Metric
R2: 1k; R_0805_2012Metric
U1A: XIAO-L; PinSocket_1x07_P2.54mm_Vertical
U1B: XIAO-R; PinSocket_1x07_P2.54mm_Vertical

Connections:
+3V3: C1.1, D1.1, J1.2, J2.2, J3.2, J4.1, J5.1, J6.1, J8.1, J10.2, R2.1, U1B.3
+5V: D2.1, J7.4, J9.2, U1B.1
D0_PIR: D4.1, J1.1, U1A.1
D1_HYDRO: D5.1, J2.1, U1A.2
D2_ULTRA: D6.1, J3.1, U1A.3
D3_EMIT: R1.1, U1A.4
EMIT_GATE: Q1.1, R1.2
EMIT_SW: D1.2, J10.1, Q1.3
GND: C1.2, D3.2, D4.2, D5.2, D6.2, J1.3, J2.3, J3.3, J4.2, J5.2, J6.2, J7.3, J8.2, J9.1, J11.2, LED1.1, Q1.2, U1B.2
LEDPWR: LED1.2, R2.2
MISO_D9: J8.4, U1B.5
MOSI_D10: J8.3, U1B.4
RX_D7: J7.1, U1B.7
SCK_D8: J8.5, U1B.6
SCL: J4.4, J5.4, J6.4, U1A.6
SDA: J4.3, J5.3, J6.3, U1A.5
TX_D6: J7.2, U1A.7
VIN: F1.2, J11.1
VPROT: D2.2, D3.1, F1.1

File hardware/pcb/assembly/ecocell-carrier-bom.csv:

Designator,Val,Package,Layer,Notes,MPN
C1,100nF,C_0805_2012Metric,top,SMT - PCBA,see FIELD-KIT.md sourcing matrix
D1,1N4148W,D_SOD-123,top,SMT - PCBA,see FIELD-KIT.md sourcing matrix
D2,SS14,D_SMA,top,SMT - PCBA,see FIELD-KIT.md sourcing matrix
D3,SMAJ5.0A,D_SMA,top,SMT - PCBA,see FIELD-KIT.md sourcing matrix
D4,PESD5V0,D_SOD-323,top,SMT - PCBA,see FIELD-KIT.md sourcing matrix
D5,PESD5V0,D_SOD-323,top,SMT - PCBA,see FIELD-KIT.md sourcing matrix
D6,PESD5V0,D_SOD-323,top,SMT - PCBA,see FIELD-KIT.md sourcing matrix
F1,0.75A,Fuse_1206_3216Metric,top,SMT - PCBA,see FIELD-KIT.md sourcing matrix
J1,PIR,PinHeader_1x03_P2.54mm_Vertical,top,THT - hand solder,see FIELD-KIT.md sourcing matrix
J2,HYDRO,PinHeader_1x03_P2.54mm_Vertical,top,THT - hand solder,see FIELD-KIT.md sourcing matrix
J3,ULTRA,PinHeader_1x03_P2.54mm_Vertical,top,THT - hand solder,see FIELD-KIT.md sourcing matrix
J4,I2C-BME280,PinHeader_1x04_P2.54mm_Vertical,top,THT - hand solder,see FIELD-KIT.md sourcing matrix
J5,I2C-BH1750,PinHeader_1x04_P2.54mm_Vertical,top,THT - hand solder,see FIELD-KIT.md sourcing matrix
J6,I2C-AD7746,PinHeader_1x04_P2.54mm_Vertical,top,THT - hand solder,see FIELD-KIT.md sourcing matrix
J7,UART,PinHeader_1x04_P2.54mm_Vertical,top,THT - hand solder,see FIELD-KIT.md sourcing matrix
J8,SPI,PinHeader_1x05_P2.54mm_Vertical,top,THT - hand solder,see FIELD-KIT.md sourcing matrix
J9,5V-IN,PinHeader_1x02_P2.54mm_Vertical,top,THT - hand solder,see FIELD-KIT.md sourcing matrix
J10,EMIT-40k,PinHeader_1x02_P2.54mm_Vertical,top,THT - hand solder,see FIELD-KIT.md sourcing matrix
J11,5V-SCREW,"TerminalBlock_Phoenix_MKDS-1,5-2_1x02_P5.00mm_Horizontal",top,THT - hand solder,see FIELD-KIT.md sourcing matrix
LED1,PWR-GRN,LED_0805_2012Metric,top,SMT - PCBA,see FIELD-KIT.md sourcing matrix
Q1,2N7002,SOT-23,top,SMT - PCBA,see FIELD-KIT.md sourcing matrix
R1,100R,R_0805_2012Metric,top,SMT - PCBA,see FIELD-KIT.md sourcing matrix
R2,1k,R_0805_2012Metric,top,SMT - PCBA,see FIELD-KIT.md sourcing matrix
U1A,XIAO-L,PinSocket_1x07_P2.54mm_Vertical,top,THT - hand solder,see FIELD-KIT.md sourcing matrix
U1B,XIAO-R,PinSocket_1x07_P2.54mm_Vertical,top,THT - hand solder,see FIELD-KIT.md sourcing matrix

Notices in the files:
hardware/pcb/ecocell-carrier.kicad_pcb:
EcoCell carrier v1 - living-resources AGPL
hardware/pcb/ecocell-node.kicad_pcb:
EcoCell One v1 - living-resources AGPL
